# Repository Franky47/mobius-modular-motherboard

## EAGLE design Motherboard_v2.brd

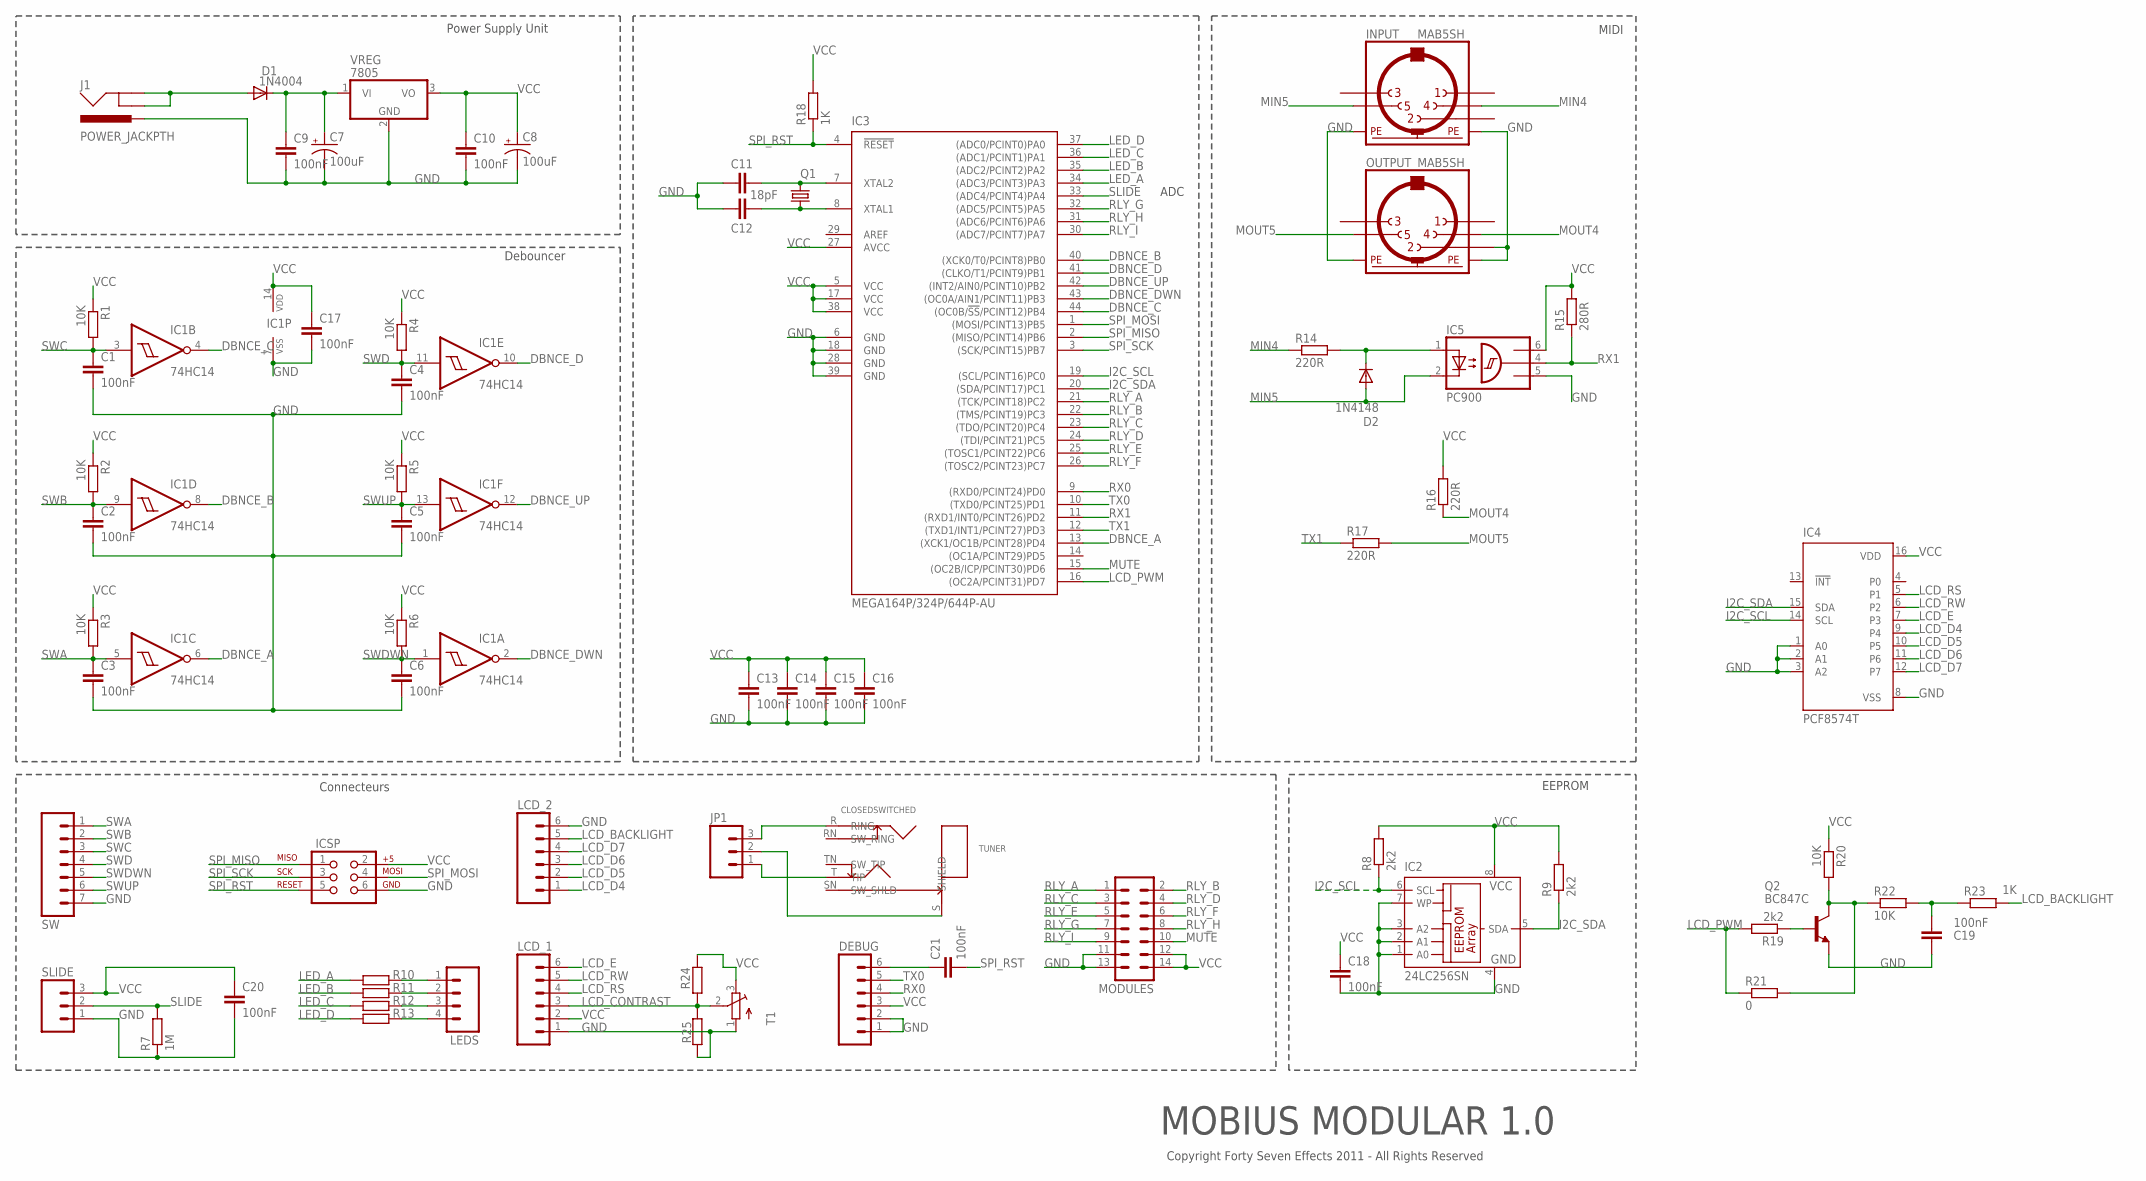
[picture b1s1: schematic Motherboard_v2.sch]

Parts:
C1, C2, C3, C4, C5, C6, C9, C10, C13, C14, C15, C16, C17, C18, C19, C20, C21: 100nF; C0805K
C7, C8: 100uF; E2,5-6E
C11, C12: 18pF; C0805K
D1: 1N4004; DO41-10
D2: 1N4148; DO35-7
DEBUG: M06SIP; 1X06
IC1: 74HC14; SO14
IC2: 24LC256SN; SO-08
IC3: MEGA164P/324P/644P-AU; TQFP44
IC4: PCF8574T; SO16W
IC5: PC900; DIL06
ICSP: AVR_SPI_PRG_6PTH; 2X3
INPUT: MAB5SH
J1: POWER_JACKPTH; POWER_JACK_PTH
JP1: M03POLAR; MOLEX-1X3
LCD_1, LCD_2: M06SIP; 1X06
LEDS: M04PTH; 1X04
MODULES: ML14
OUTPUT: MAB5SH
Q1: 16MHz; CRYSTAL-SMD-5X3
Q2: BC847C; SOT23
R1, R2, R3, R4, R5, R6, R20, R22: 10K; M0805
R7: 1M; M0805
R8, R9, R19: 2k2; M0805
R10, R12, R13, R24, R25: 1k; M0805
R11, R18, R23: 1K; M0805
R14, R16, R17: 220R; M0805
R15: 280R; M0805
R21: 0; M0805
SLIDE: M03PTH; 1X03
SW: M07; 1X07
T1: TRIMPOTTC33X; TC33X
TUNER: CLOSEDSWITCHED; NMJ6HFD2
VREG: 7805; TO220V

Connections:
AREF: IC3.29 (AREF)
DBNCE_A: IC1.6 (O), IC3.13 ((XCK1/OC1B/PCINT28)PD4)
DBNCE_B: IC1.8 (O), IC3.40 ((XCK0/T0/PCINT8)PB0)
DBNCE_C: IC1.4 (O), IC3.44 ((OC0B/!SS!/PCINT12)PB4)
DBNCE_D: IC1.10 (O), IC3.41 ((CLKO/T1/PCINT9)PB1)
DBNCE_DWN: IC1.2 (O), IC3.43 ((OC0A/AIN1/PCINT11)PB3)
DBNCE_UP: IC1.12 (O), IC3.42 ((INT2/AIN0/PCINT10)PB2)
GND: C1.2, C2.2, C3.2, C4.2, C5.2, C6.2, C7.-, C8.-, C9.2, C10.2, C11.1, C12.1, C13.2, C14.2, C15.2, C16.2, C17.2, C18.2, C19.1, C20.2, DEBUG.1, DEBUG.2, IC1.7 (VSS), IC2.1 (A0), IC2.2 (A1), IC2.3 (A2), IC2.4 (GND), IC2.7 (WP), IC3.6 (GND), IC3.18 (GND), IC3.28 (GND), IC3.39 (GND), IC4.1 (A0), IC4.2 (A1), IC4.3 (A2), IC4.8 (VSS), IC5.5 (GND), ICSP.6, INPUT.PE, INPUT.PE@ (PE), J1.PWR, LCD_1.1, LCD_2.6, MODULES.11, MODULES.13, OUTPUT.2, OUTPUT.PE, OUTPUT.PE@ (PE), Q2.2 (E), R7.1, R25.1, SLIDE.1, SW.7, T1.1 (A), VREG.2 (GND)
I2C_SCL: IC2.6 (SCL), IC3.19 ((SCL/PCINT16)PC0), IC4.14 (SCL), R8.1
I2C_SDA: IC2.5 (SDA), IC3.20 ((SDA/PCINT17)PC1), IC4.15 (SDA), R9.1
LCD_BACKLIGHT: LCD_2.5, R23.2
LCD_CONTRAST: LCD_1.3, R24.1, R25.2, T1.2 (S)
LCD_D4: IC4.9 (P4), LCD_2.1
LCD_D5: IC4.10 (P5), LCD_2.2
LCD_D6: IC4.11 (P6), LCD_2.3
LCD_D7: IC4.12 (P7), LCD_2.4
LCD_E: IC4.7 (P3), LCD_1.6
LCD_PWM: IC3.16 ((OC2A/PCINT31)PD7), R19.2, R21.1
LCD_RS: IC4.5 (P1), LCD_1.4
LCD_RW: IC4.6 (P2), LCD_1.5
LED_A: IC3.34 ((ADC3/PCINT3)PA3), R10.1
LED_B: IC3.35 ((ADC2/PCINT2)PA2), R11.1
LED_C: IC3.36 ((ADC1/PCINT1)PA1), R12.1
LED_D: IC3.37 ((ADC0/PCINT0)PA0), R13.1
MIN4: INPUT.4, R14.1
MIN5: D2.A, IC5.2 (C), INPUT.5
MOUT4: OUTPUT.4, R16.1
MOUT5: OUTPUT.5, R17.2
MUTE: IC3.15 ((OC2B/ICP/PCINT30)PD6), MODULES.10
unnamed: C7.+, C9.1, D1.C, VREG.1 (VI)
unnamed: LEDS.1, R10.2
unnamed: LEDS.2, R11.2
unnamed: D1.A, J1.GND, J1.GNDBREAK
unnamed: LEDS.3, R12.2
unnamed: D2.C, IC5.1 (A), R14.2
unnamed: LEDS.4, R13.2
unnamed: C11.2, IC3.7 (XTAL2), Q1.3 (2)
unnamed: C12.2, IC3.8 (XTAL1), Q1.1
unnamed: JP1.1, TUNER.T (TIP)
unnamed: JP1.3, TUNER.R (RING)
unnamed: JP1.2, TUNER.S (SHIELD)
unnamed: Q2.1 (B), R19.1
unnamed: Q2.3 (C), R20.2, R21.2, R22.1
unnamed: C19.2, R22.2, R23.1
unnamed: C21.1, DEBUG.6
RLY_A: IC3.21 ((TCK/PCINT18)PC2), MODULES.1
RLY_B: IC3.22 ((TMS/PCINT19)PC3), MODULES.2
RLY_C: IC3.23 ((TDO/PCINT20)PC4), MODULES.3
RLY_D: IC3.24 ((TDI/PCINT21)PC5), MODULES.4
RLY_E: IC3.25 ((TOSC1/PCINT22)PC6), MODULES.5
RLY_F: IC3.26 ((TOSC2/PCINT23)PC7), MODULES.6
RLY_G: IC3.32 ((ADC5/PCINT5)PA5), MODULES.7
RLY_H: IC3.31 ((ADC6/PCINT6)PA6), MODULES.8
RLY_I: IC3.30 ((ADC7/PCINT7)PA7), MODULES.9
RX0: DEBUG.4, IC3.9 ((RXD0/PCINT24)PD0)
RX1: IC3.11 ((RXD1/INT0/PCINT26)PD2), IC5.4 (OUT), R15.1
SLIDE: IC3.33 ((ADC4/PCINT4)PA4), R7.2, SLIDE.2
SPI_MISO: IC3.2 ((MISO/PCINT14)PB6), ICSP.1
SPI_MOSI: IC3.1 ((MOSI/PCINT13)PB5), ICSP.4
SPI_RST: C21.2, IC3.4 (!RESET), ICSP.5, R18.1
SPI_SCK: IC3.3 ((SCK/PCINT15)PB7), ICSP.3
SWA: C3.1, IC1.5 (I), R3.2, SW.1
SWB: C2.1, IC1.9 (I), R2.2, SW.2
SWC: C1.1, IC1.3 (I), R1.2, SW.3
SWD: C4.1, IC1.11 (I), R4.2, SW.4
SWDWN: C6.1, IC1.1 (I), R6.2, SW.5
SWUP: C5.1, IC1.13 (I), R5.2, SW.6
TX0: DEBUG.5, IC3.10 ((TXD0/PCINT25)PD1)
TX1: IC3.12 ((TXD1/INT1/PCINT27)PD3), R17.1
VCC: C8.+, C10.1, C13.1, C14.1, C15.1, C16.1, C17.1, C18.1, C20.1, DEBUG.3, IC1.14 (VDD), IC2.8 (VCC), IC3.5 (VCC), IC3.17 (VCC), IC3.27 (AVCC), IC3.38 (VCC), IC4.16 (VDD), IC5.6 (VCC), ICSP.2, LCD_1.2, MODULES.12, MODULES.14, R1.1, R2.1, R3.1, R4.1, R5.1, R6.1, R8.2, R9.2, R15.2, R16.2, R18.2, R20.1, R24.2, SLIDE.3, T1.3 (E), VREG.3 (VO)

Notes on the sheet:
Debouncer
Power Supply Unit
EEPROM
MIDI
Connecteurs
MOBIUS MODULAR 1.0
Copyright Forty Seven Effects 2011 - All Rights Reserved
ADC

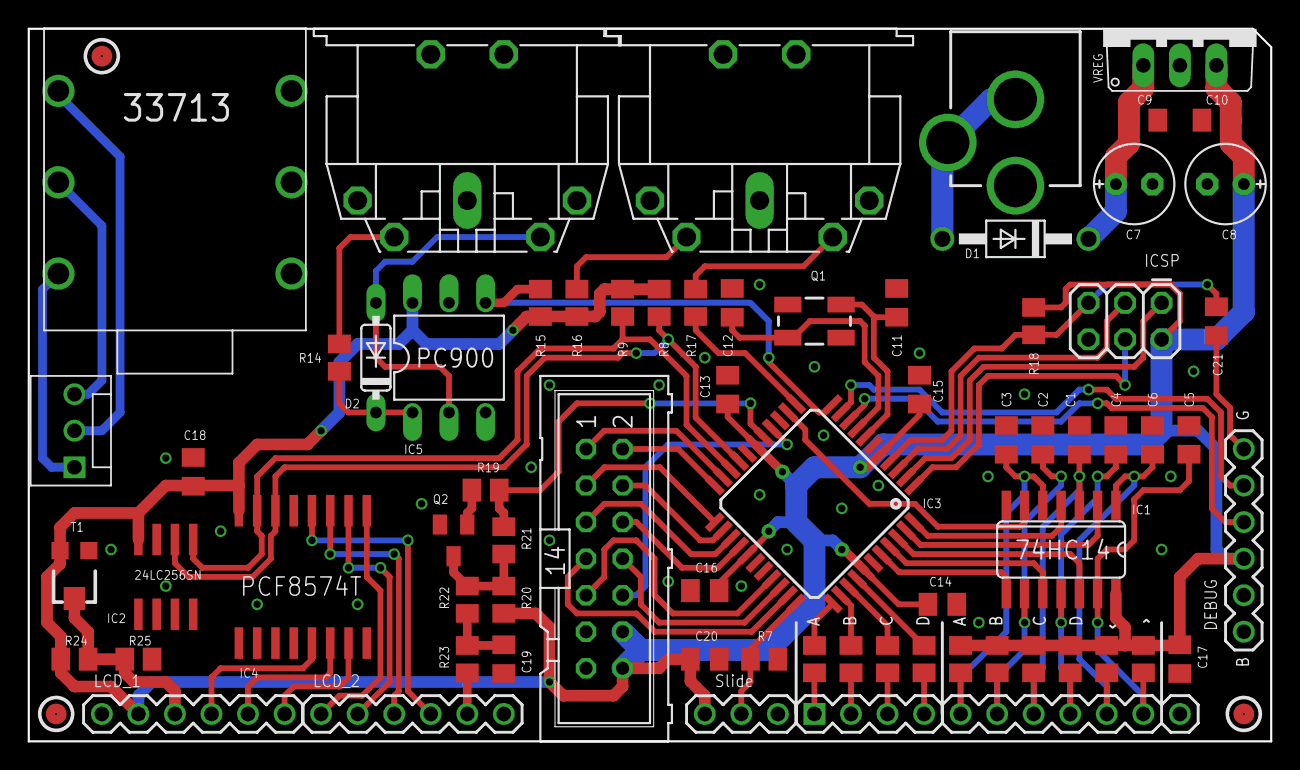
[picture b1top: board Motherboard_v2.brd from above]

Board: 2 copper layers, 86.4 x 49.5 mm, 71 parts (1 on the bottom side), 69 nets.

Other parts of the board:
U$1: FSE-LOGOTITLE

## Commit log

2017-01-03 Removed temp file.
